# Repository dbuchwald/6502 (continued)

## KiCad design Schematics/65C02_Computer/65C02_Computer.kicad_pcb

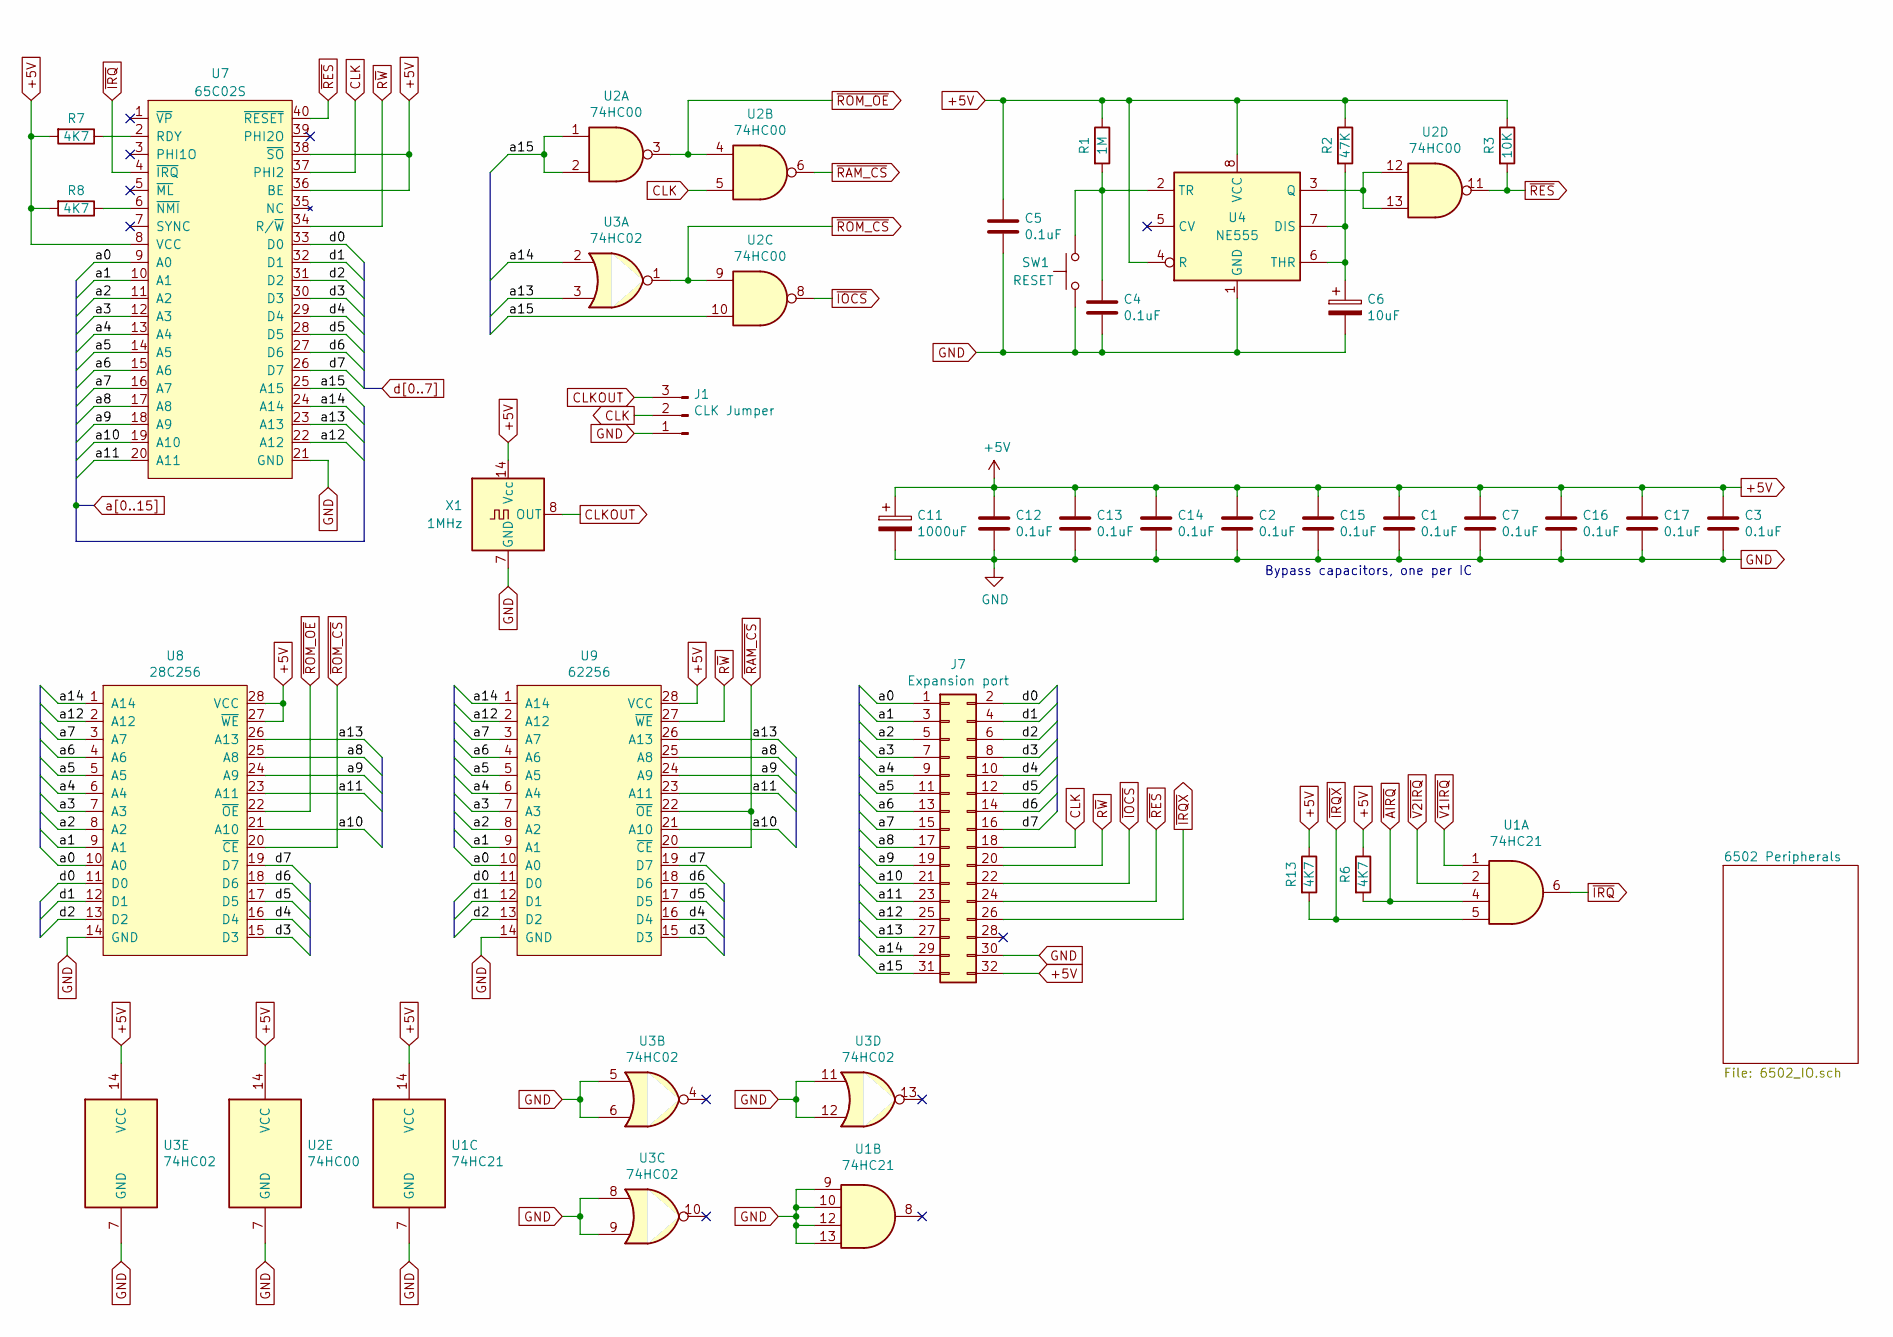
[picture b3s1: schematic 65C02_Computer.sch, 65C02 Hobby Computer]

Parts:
C1, C2, C3, C4, C5, C7, C12, C13, C14, C15, C16, C17: 0.1uF; C_Disc_D3.4mm_W2.1mm_P2.50mm
C6: 10uF; CP_Radial_D5.0mm_P2.50mm
C11: 1000uF; CP_Radial_D10.0mm_P5.00mm
J1: CLK Jumper; PinHeader_1x03_P2.54mm_Vertical
J7: Expansion port; PinSocket_2x16_P2.54mm_Vertical
R1: 1M; R_Axial_DIN0207_L6.3mm_D2.5mm_P7.62mm_Horizontal
R2: 47K; R_Axial_DIN0207_L6.3mm_D2.5mm_P7.62mm_Horizontal
R3: 10K; R_Axial_DIN0207_L6.3mm_D2.5mm_P7.62mm_Horizontal
R6, R7, R8, R13: 4K7; R_Axial_DIN0207_L6.3mm_D2.5mm_P7.62mm_Horizontal
SW1: RESET; SW_PUSH_6mm_H4.3mm
U1: 74HC21; DIP-14_W7.62mm_Socket
U2: 74HC00; DIP-14_W7.62mm_Socket
U3: 74HC02; DIP-14_W7.62mm_Socket
U4: NE555; DIP-8_W7.62mm_Socket
U7: 65C02S; DIP-40_W15.24mm_Socket
U8: 28C256; DIP-28_W15.24mm_Socket
U9: 62256; DIP-28_W15.24mm_Socket
X1: 1MHz; Oscillator_DIP-14

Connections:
+5V: C1.1, C2.1, C3.1, C5.1, C7.1, C11.1, C12.1, C13.1, C14.1, C15.1, C16.1, C17.1, J7.32, R1.1, R2.1, R3.1, R6.1, R7.2, R8.2, R13.1, U1.14 (VCC), U2.14 (VCC), U3.14 (VCC), U4.4 (R), U4.8 (VCC), U7.8 (VCC), U7.36 (BE), U7.38 (~SO), U8.27 (~WE), U8.28 (VCC), U9.28 (VCC), X1.14 (Vcc); also elsewhere on the board
CLK: J1.2, J7.18, U2.5, U7.37 (PHI2); also elsewhere on the board
CLKOUT: J1.3, X1.8 (OUT)
GND: C1.2, C2.2, C3.2, C4.2, C5.2, C6.2, C7.2, C11.2, C12.2, C13.2, C14.2, C15.2, C16.2, C17.2, J1.1, J7.30, SW1.1, U1.7 (GND), U1.9, U1.10, U1.12, U1.13, U2.7 (GND), U3.5, U3.6, U3.7 (GND), U3.8, U3.9, U3.11, U3.12, U4.1 (GND), U7.21 (GND), U8.14 (GND), U9.14 (GND), X1.7 (GND); also elsewhere on the board
unnamed: C4.1, R1.2, SW1.2, U4.2 (TR)
unnamed: C6.1, R2.2, U4.6 (THR), U4.7 (DIS)
unnamed: R7.1, U7.2 (RDY)
unnamed: R8.1, U7.6 (~NMI)
unnamed: U2.12, U2.13, U4.3 (Q)
R~W: J7.20, U7.34 (R/~W), U9.27 (~WE); also elsewhere on the board
a0: J7.1, U7.9 (A0), U8.10 (A0), U9.10 (A0); also elsewhere on the board
a1: J7.3, U7.10 (A1), U8.9 (A1), U9.9 (A1); also elsewhere on the board
a2: J7.5, U7.11 (A2), U8.8 (A2), U9.8 (A2); also elsewhere on the board
a3: J7.7, U7.12 (A3), U8.7 (A3), U9.7 (A3); also elsewhere on the board
a4: J7.9, U7.13 (A4), U8.6 (A4), U9.6 (A4)
a5: J7.11, U7.14 (A5), U8.5 (A5), U9.5 (A5)
a6: J7.13, U7.15 (A6), U8.4 (A6), U9.4 (A6)
a7: J7.15, U7.16 (A7), U8.3 (A7), U9.3 (A7)
a8: J7.17, U7.17 (A8), U8.25 (A8), U9.25 (A8)
a9: J7.19, U7.18 (A9), U8.24 (A9), U9.24 (A9)
a10: J7.21, U7.19 (A10), U8.21 (A10), U9.21 (A10); also elsewhere on the board
a11: J7.23, U7.20 (A11), U8.23 (A11), U9.23 (A11); also elsewhere on the board
a12: J7.25, U7.22 (A12), U8.2 (A12), U9.2 (A12); also elsewhere on the board
a13: J7.27, U3.3, U7.23 (A13), U8.26 (A13), U9.26 (A13)
a14: J7.29, U3.2, U7.24 (A14), U8.1 (A14), U9.1 (A14)
a15: J7.31, U2.1, U2.2, U2.10, U7.25 (A15)
d0: J7.2, U7.33 (D0), U8.11 (D0), U9.11 (D0); also elsewhere on the board
d1: J7.4, U7.32 (D1), U8.12 (D1), U9.12 (D1); also elsewhere on the board
d2: J7.6, U7.31 (D2), U8.13 (D2), U9.13 (D2); also elsewhere on the board
d3: J7.8, U7.30 (D3), U8.15 (D3), U9.15 (D3); also elsewhere on the board
d4: J7.10, U7.29 (D4), U8.16 (D4), U9.16 (D4); also elsewhere on the board
d5: J7.12, U7.28 (D5), U8.17 (D5), U9.17 (D5); also elsewhere on the board
d6: J7.14, U7.27 (D6), U8.18 (D6), U9.18 (D6); also elsewhere on the board
d7: J7.16, U7.26 (D7), U8.19 (D7), U9.19 (D7); also elsewhere on the board
~AIRQ: R6.2, U1.4; also elsewhere on the board
~IOCS: J7.22, U2.8; also elsewhere on the board
~IRQ: U1.6, U7.4 (~IRQ)
~IRQX: J7.26, R13.2, U1.5
~RAM_CS: U2.6, U9.20 (~CE), U9.22 (~OE)
~RES: J7.24, R3.2, U2.11, U7.40 (~RESET); also elsewhere on the board
~ROM_CS: U2.9, U3.1, U8.20 (~CE)
~ROM_OE: U2.3, U2.4, U8.22 (~OE)
~V1IRQ: U1.1; also elsewhere on the board
~V2IRQ: U1.2; also elsewhere on the board

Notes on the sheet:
Bypass capacitors, one per IC

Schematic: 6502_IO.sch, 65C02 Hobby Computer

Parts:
C8: 10nF; C_Disc_D3.4mm_W2.1mm_P2.50mm
C9, C10: 47pF; C_Disc_D3.4mm_W2.1mm_P2.50mm
D1: PWR; LED_D5.0mm_Clear
D2: TX; LED_D5.0mm_Clear
D3: RX; LED_D5.0mm_Clear
D4: BLINK; LED_D5.0mm_Clear
FB1: Ferrite_Bead_Small; R_Axial_DIN0207_L6.3mm_D2.5mm_P7.62mm_Horizontal
J2: Optional UART Port; PinSocket_1x06_P2.54mm_Vertical
J3: USB_B_Micro; USB_Micro-B_Molex-105017-0001
J4: USB_B; USB_B_OST_USB-B1HSxx_Horizontal
J5: Power Connector; BarrelJack_Horizontal
J6: Mini-DIN-6; mini_din-6
J8: AVR-ISP-10; PinHeader_2x03_P2.54mm_Vertical
J9: VIA2PA; PinHeader_1x12_P2.54mm_Vertical
J10: VIA2PB; PinHeader_1x12_P2.54mm_Vertical
J11: LCD Connector; PinSocket_1x16_P2.54mm_Vertical
R4, R5: 27; R_Axial_DIN0207_L6.3mm_D2.5mm_P7.62mm_Horizontal
R9, R10, R11, R12: 270; R_Axial_DIN0207_L6.3mm_D2.5mm_P7.62mm_Horizontal
RV1: 10K; Potentiometer_Piher_PT-10-V10_Vertical
U5: 65C51N; DIP-28_W15.24mm_Socket
U6: FT230XS; SSOP-16_3.9x4.9mm_P0.635mm_long_pads
U10: ATtiny4313-PU; DIP-20_W7.62mm_Socket
U11, U12: 65C22S; DIP-40_W15.24mm_Socket
X2: 1.8432MHz; Oscillator_DIP-14

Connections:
+5V: C8.1, FB1.1, J2.6, J5.1, J6.4, J8.2, J9.12, J10.12, J11.2, J11.15, R12.1, RV1.1, U5.15 (VDD), U6.12 (VCC), U10.20 (VCC), U11.20 (VDD), U12.20 (VDD), X2.14 (Vcc); also elsewhere on the board
/6502 Peripherals/v1pa0: U10.12 (PB0), U12.2 (PA0)
/6502 Peripherals/v1pa1: U10.13 (PB1), U12.3 (PA1)
/6502 Peripherals/v1pa2: U10.14 (PB2), U12.4 (PA2)
/6502 Peripherals/v1pa3: U10.15 (PB3), U12.5 (PA3)
/6502 Peripherals/v1pa4: U10.16 (PB4), U12.6 (PA4)
/6502 Peripherals/v1pa5: J8.4, U10.17 (PB5), U12.7 (PA5)
/6502 Peripherals/v1pa6: J8.1, U10.18 (PB6), U12.8 (PA6)
/6502 Peripherals/v1pa7: J8.3, U10.19 (PB7), U12.9 (PA7)
/6502 Peripherals/v1pa8: U10.3 (PD1), U12.40 (CA1)
/6502 Peripherals/v1pa9: U10.7 (PD3), U12.39 (CA2)
/6502 Peripherals/v1pb0: R9.1, U12.10 (PB0)
/6502 Peripherals/v1pb1: J11.4, U12.11 (PB1)
/6502 Peripherals/v1pb2: J11.5, U12.12 (PB2)
/6502 Peripherals/v1pb3: J11.6, U12.13 (PB3)
/6502 Peripherals/v1pb4: J11.11, U12.14 (PB4)
/6502 Peripherals/v1pb5: J11.12, U12.15 (PB5)
/6502 Peripherals/v1pb6: J11.13, U12.16 (PB6)
/6502 Peripherals/v1pb7: J11.14, U12.17 (PB7)
/6502 Peripherals/v2pa0: J9.1, U11.2 (PA0)
/6502 Peripherals/v2pa1: J9.2, U11.3 (PA1)
/6502 Peripherals/v2pa2: J9.3, U11.4 (PA2)
/6502 Peripherals/v2pa3: J9.4, U11.5 (PA3)
/6502 Peripherals/v2pa4: J9.5, U11.6 (PA4)
/6502 Peripherals/v2pa5: J9.6, U11.7 (PA5)
/6502 Peripherals/v2pa6: J9.7, U11.8 (PA6)
/6502 Peripherals/v2pa7: J9.8, U11.9 (PA7)
/6502 Peripherals/v2pa8: J9.9, U11.40 (CA1)
/6502 Peripherals/v2pa9: J9.10, U11.39 (CA2)
/6502 Peripherals/v2pb0: J10.1, U11.10 (PB0)
/6502 Peripherals/v2pb1: J10.2, U11.11 (PB1)
/6502 Peripherals/v2pb2: J10.3, U11.12 (PB2)
/6502 Peripherals/v2pb3: J10.4, U11.13 (PB3)
/6502 Peripherals/v2pb4: J10.5, U11.14 (PB4)
/6502 Peripherals/v2pb5: J10.6, U11.15 (PB5)
/6502 Peripherals/v2pb6: J10.7, U11.16 (PB6)
/6502 Peripherals/v2pb7: J10.8, U11.17 (PB7)
/6502 Peripherals/v2pb8: J10.9, U11.18 (CB1)
/6502 Peripherals/v2pb9: J10.10, U11.19 (CB2)
CLK: U5.27 (PHI2), U11.25 (PHI2), U12.25 (PHI2); also elsewhere on the board
GND: C8.2, C9.2, C10.2, D1.1 (K), D4.1 (K), J2.5, J3.5 (GND), J4.4 (GND), J5.2, J6.3, J8.6, J9.11, J10.11, J11.1, J11.7, J11.8, J11.9, J11.10, J11.16, RV1.3, U5.1 (VSS), U5.16 (~DCD), U5.17 (~DSR), U6.5 (GND), U6.13 (GND), U10.10 (GND), U11.1 (VSS), U12.1 (VSS), X2.7 (GND); also elsewhere on the board
KBCLK: J6.5, U10.6 (PD2)
KBDAT: J6.1, U10.2 (PD0)
unnamed: D1.2 (A), R12.2
unnamed: D2.1 (K), U6.15 (CBUS0)
unnamed: D2.2 (A), R11.2
unnamed: D3.1 (K), U6.14 (CBUS1)
unnamed: D3.2 (A), R10.2
unnamed: D4.2 (A), R9.2
unnamed: FB1.2, J3.1 (VBUS), J4.1 (VBUS)
unnamed: J11.3, RV1.2
unnamed: R10.1, R11.1, U6.3 (VCCIO), U6.10 (3V3OUT)
PUSBD+: C9.1, J3.3 (D+), J4.3 (D+), R5.2
PUSBD-: C10.1, J3.2 (D-), J4.2 (D-), R4.2
RS232CLK: U5.6 (XTLI), X2.8 (OUT)
RxD: J2.2, U5.12 (RxD), U6.1 (TXD)
R~W: U5.28 (R~W), U11.22 (R~W), U12.22 (R~W); also elsewhere on the board
TxD: J2.1, U5.10 (TxD), U6.4 (RXD)
USBD+: R5.1, U6.8 (USBD+)
USBD-: R4.1, U6.9 (USBD-)
a0: U5.13 (RS0), U11.38 (RS0), U12.38 (RS0); also elsewhere on the board
a1: U5.14 (RS1), U11.37 (RS1), U12.37 (RS1); also elsewhere on the board
a2: U11.36 (RS2), U12.36 (RS2); also elsewhere on the board
a3: U11.35 (RS3), U12.35 (RS3); also elsewhere on the board
a10: U5.2 (CS0); also elsewhere on the board
a11: U11.24 (CS1); also elsewhere on the board
a12: U12.24 (CS1); also elsewhere on the board
d0: U5.18 (D0), U11.33 (D0), U12.33 (D0); also elsewhere on the board
d1: U5.19 (D1), U11.32 (D1), U12.32 (D1); also elsewhere on the board
d2: U5.20 (D2), U11.31 (D2), U12.31 (D2); also elsewhere on the board
d3: U5.21 (D3), U11.30 (D3), U12.30 (D3); also elsewhere on the board
d4: U5.22 (D4), U11.29 (D4), U12.29 (D4); also elsewhere on the board
d5: U5.23 (D5), U11.28 (D5), U12.28 (D5); also elsewhere on the board
d6: U5.24 (D6), U11.27 (D6), U12.27 (D6); also elsewhere on the board
d7: U5.25 (D7), U11.26 (D7), U12.26 (D7); also elsewhere on the board
~AIRQ: U5.26 (~IRQ); also elsewhere on the board
~CTS: J2.4, U5.9 (~CTS), U6.2 (~RTS)
~IOCS: U5.3 (~CS1), U11.23 (~CS2), U12.23 (~CS2); also elsewhere on the board
~RES: J8.5, U5.4 (~RES), U6.11 (~RES), U10.1 (PA2/~RESET), U11.34 (~RES), U12.34 (~RES); also elsewhere on the board
~RTS: J2.3, U5.8 (~RTS), U6.6 (~CTS)
~V1IRQ: U12.21 (~IRQ); also elsewhere on the board
~V2IRQ: U11.21 (~IRQ); also elsewhere on the board

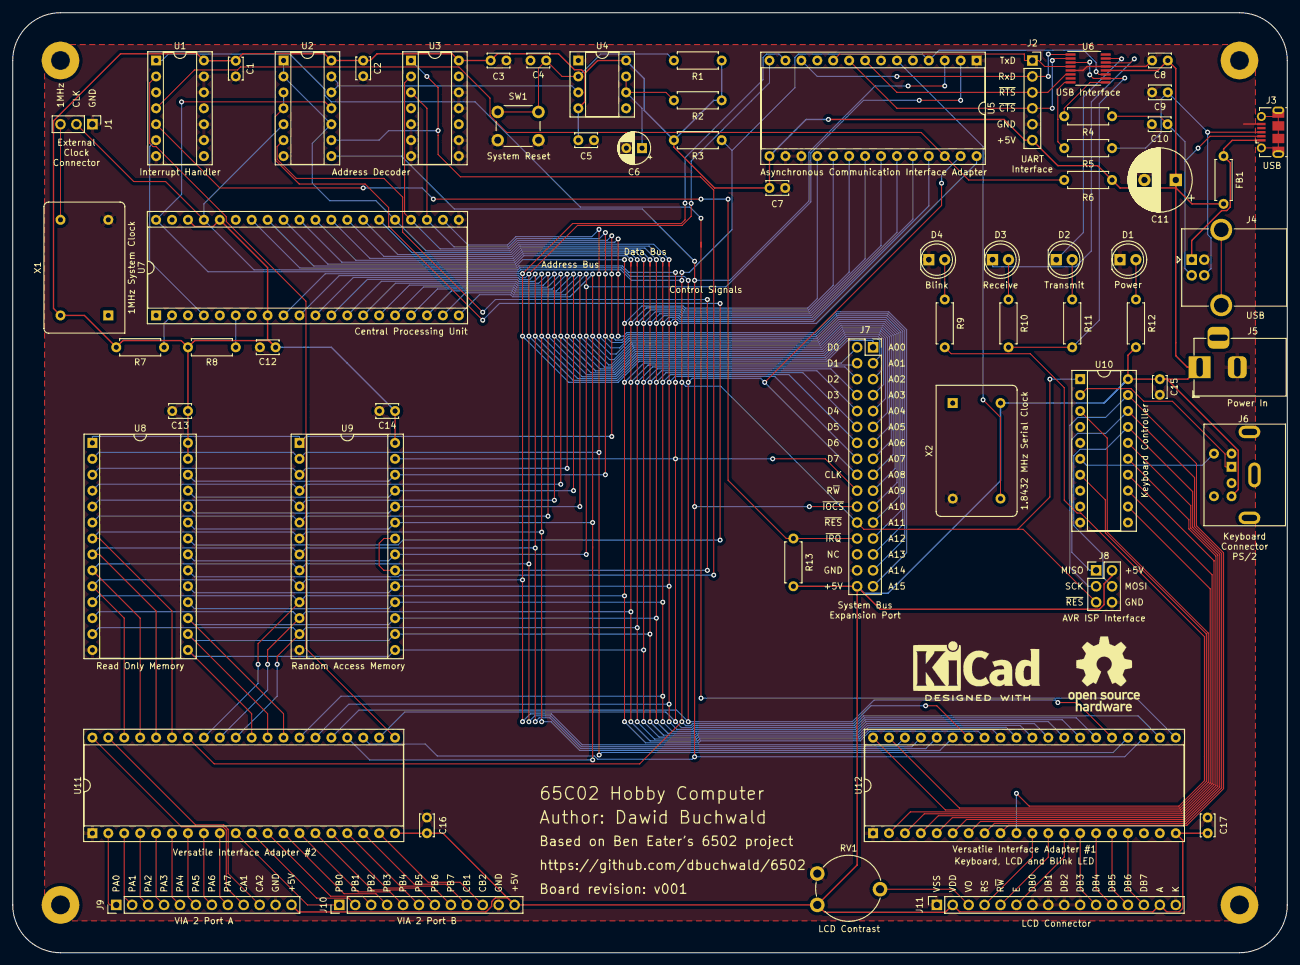
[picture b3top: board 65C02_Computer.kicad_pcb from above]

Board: 2 copper layers, 203.2 x 149.9 mm, 62 parts (0 on the bottom side), 102 nets.

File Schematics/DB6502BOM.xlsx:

Reference | Type | Value | Description | Jameco | DigiKey
C1 | Unpolarized Capacitor | 100 nF | Disk, 2.5mm raster | 151116 | 399-4151-ND
C2 | Unpolarized Capacitor | 100 nF | Disk, 2.5mm raster | 151116 | 399-4151-ND
C3 | Unpolarized Capacitor | 100 nF | Disk, 2.5mm raster | 151116 | 399-4151-ND
C4 | Unpolarized Capacitor | 100 nF | Disk, 2.5mm raster | 151116 | 399-4151-ND
C5 | Unpolarized Capacitor | 100 nF | Disk, 2.5mm raster | 151116 | 399-4151-ND
C6 | Polarized Capacitor | 10 uF | Tube, 2.5mm raster, 5mm diameter | 330692 | 1189-2322-ND
C7 | Unpolarized Capacitor | 100 nF | Disk, 2.5mm raster | 151116 | 399-4151-ND
C8 | Unpolarized Capacitor | 10 nF | Disk, 2.5mm raster |  | 399-4150-ND
C9 | Unpolarized Capacitor | 47 pF | Disk, 2.5mm raster | 2300831 | 399-9737-ND
C10 | Unpolarized Capacitor | 47 pF | Disk, 2.5mm raster | 2300831 | 399-9737-ND
C11 | Polarized Capacitor | 1000 uF | Tube, 5mm raster, 10mm diameter | 330722 | 1189-1745-ND
C12 | Unpolarized Capacitor | 100 nF | Disk, 2.5mm raster | 151116 | 399-4151-ND
C13 | Unpolarized Capacitor | 100 nF | Disk, 2.5mm raster | 151116 | 399-4151-ND
C14 | Unpolarized Capacitor | 100 nF | Disk, 2.5mm raster | 151116 | 399-4151-ND
C15 | Unpolarized Capacitor | 100 nF | Disk, 2.5mm raster | 151116 | 399-4151-ND
C16 | Unpolarized Capacitor | 100 nF | Disk, 2.5mm raster | 151116 | 399-4151-ND
C17 | Unpolarized Capacitor | 100 nF | Disk, 2.5mm raster | 151116 | 399-4151-ND
D1 | LED | Green | 5mm diameter (PWR) | 2279199 | 754-1263-ND
D2 | LED | Red | 5mm diameter (TX) | 333973 | 754-1264-ND
D3 | LED | Green | 5mm diameter (RX) | 2279199 | 754-1263-ND
D4 | LED | Red | 5mm diameter (BLINK) | 333973 | 754-1264-ND
FB1 | Ferrite bead small |  |  | 1844580 | 490-10997-ND
J1 | Pin header 3x1 |  | 2.54mm raster |  | 2057-PH1-03-UA-ND
J2 | Female pin header 6x1 |  | 2.54mm raster |  | S7004-ND
J3 | USB B Micro |  | Molex 105017-0001 |  | WM1399CT-ND
J4 | USB B |  | Standard THT horizontal USB B port | 2096245 | 2057-USB-B-S-RA-ND
J5 | Barrel Jack |  | Standard power input 2.1/5.5 | 101178
J6 | Mini-Din-6 |  | Standard THT PS/2 Keyboard port | 119475 | CP-2260-ND
J7 | Female pin header 16x2 |  | 2.54mm raster |  | S7119-ND
J8 | Pin header 3x2 |  | AVR ISP 2.54mm raster |  | 609-3234-ND
J9 | Pin header 12x1 |  | 2.54mm raster |  | 2057-PH1-12-UA-ND
J10 | Pin header 12x1 |  | 2.54mm raster |  | 2057-PH1-12-UA-ND
J11 | Female pin header 16x1 |  | 2.54mm raster |  | S7049-ND
R1 | Resistor | 1M | 1/4 watt | 691585
R2 | Resistor | 47K | 1/4 watt | 691260
R3 | Resistor | 10K | 1/4 watt | 691104
R4 | Resistor | 27 | 1/4 watt | 690486
R5 | Resistor | 27 | 1/4 watt | 690486
R6 | Resistor | 4K7 | 1/4 watt | 691024
R7 | Resistor | 4K7 | 1/4 watt | 691024
R8 | Resistor | 4K7 | 1/4 watt | 691024
R9 | Resistor | 220 | 1/4 watt | 690700
R10 | Resistor | 220 | 1/4 watt | 690700
R11 | Resistor | 220 | 1/4 watt | 690700
R12 | Resistor | 220 | 1/4 watt | 690700
R13 | Resistor | 4K7 | 1/4 watt | 691260
RV1 | Potentiometer | 10K | Piher PT10-LV10-103 |  | 1993-1116-ND
SW1 | Pushbutton |  | Standard 6mm THT pushbutton | 149948
U1 | IC | 74HC21 |  | 2285255 | 296-8266-5-ND
U1 | Socket | 14-pin |  | 37197 | ED3314-ND
U2 | IC | 74HC00 |  | 45161 | 296-1563-5-ND
U2 | Socket | 14-pin |  | 37197 | ED3314-ND
U3 | IC | 74HC02 |  | 45188 | 296-1564-5-ND
U3 | Socket | 14-pin |  | 37197 | ED3314-ND
U4 | IC | NE555 |  | 27422 | 296-NE555P-ND
U4 | Socket | 8-pin |  | 51626 | ED90048-ND
U5 | IC | 6551 | ACIA chip, see notes below | 43318
U6 | IC | FT230XS |  |  | 768-1135-1-ND
U7 | IC | 65C02S |  | 2143638
U7 | Socket | 40-pin |  | 41136 | ED90059-ND
U8 | IC | 28C256 |  | 74843 | AT28C256-15PU-ND
U8 | Socket | 28-pin | Order two | 2289583 | ED90520-ND
U9 | IC | 62256 |  | 82472 | 1450-1480-ND
U9 | Socket | 28-pin |  | 2289583 | ED90520-ND
U10 | IC | ATtiny4313-PU | Add socket |  | ATTINY4313-PU-ND
U10 | Socket | 20-pin |  | 38623 | ED90036-ND
U11 | IC | 65C22S |  | 2143591
U11 | Socket | 40-pin |  | 41136 | ED90059-ND
U12 | IC | 65C22S |  | 2143591
U12 | Socket | 40-pin |  | 41136 | ED90059-ND
X1 | Crystal Oscillator | 1MHz |  | 27861 | X937-ND
X2 | Crystal Oscillator | 1.8432MHz |  | 27879 | X939-ND

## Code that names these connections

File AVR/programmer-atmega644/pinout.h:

#ifndef __PINOUT_H__DEFINED
#define __PINOUT_H__DEFINED

#define ADDRMSB_DDR  DDRC
#define ADDRLSB_DDR  DDRA
#define DATA_DDR     DDRB
#define CONTROL_DDR  DDRD

#define ADDRMSB_POUT PORTC
#define ADDRLSB_POUT PORTA
#define DATA_POUT    PORTB
#define CONTROL_POUT PORTD

#define ADDRMSB_PIN  PINC
#define ADDRLSB_PIN  PINA
#define DATA_PIN     PINB
#define CONTROL_PIN  PIND

#define SR_DAT       _BV(PD2)
#define SR_CLK       _BV(PD3)
#define SR_OUT       _BV(PD4)

#define CLK_BIT      _BV(PD5)
#define RW_BIT       _BV(PD6)
#define SYNC_BIT     _BV(PD7)

#define CLKSEL_BIT   _BV(0)
#define BE_BIT       _BV(1)
#define RDY_BIT      _BV(2)
#define RESET_BIT    _BV(7)

#define ALL_INPUT    0x00
#define ALL_OUTPUT   0xff
#define ALL_PULL_UP  0xff

#endif

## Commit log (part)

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2020-04-01 Changed ZP variable name
2020-04-01 Added missing message
2020-04-01 Added system break test
2020-04-02 Major rebranding and credits
2020-04-02 Create LICENSE
2020-04-02 Added tokenize tests to string testing module
2020-04-03 First implementation of generic menu feature
2020-04-04 Implemented basic parse functions
2020-04-04 Moved parser and menu routines to common library
2020-04-05 Corrected macro
2020-04-05 Refactoring in progress
2020-04-05 Fixed system break bug
2020-04-05 Fixed broken macro
2020-04-05 Fixed parse issue
2020-04-05 Reimplemented monitor and simple shell using menu
2020-04-06 Address mode refactoring
2020-04-06 Initial monitor implementation
2020-04-07 Implemented missing LCD TTY routines, fixed some bugs
2020-04-07 Common library analyzed for C compatibility
2020-04-07 Added opcodes matrix for disassembler
2020-04-08 Corrected issue #34
    Corrected pot value for clock frequency regulator
2020-04-08 Moved strcpy to common string routines
2020-04-08 Added disassembly function to monitor app
2020-04-09 Resolved #36, partially implemented #28
2020-04-10 Initial implementation - not working
2020-04-10 Updated parse routines
2020-04-10 Refactored blink operation, added C bindings
2020-04-10 Provided ACIA bindings for C
2020-04-11 Fixed issue with last commit
2020-04-14 Implemented C bindings for LCD
2020-04-14 Added C bindings for some C functions
2020-04-14 C bindins for TTY operations
2020-04-14 Fixed issue with disassembler operation
2020-04-15 Added remaining string functions C bindings
2020-04-15 Created C bindings for remaining LCD routines
2020-04-15 C bindings for parse functions
2020-04-15 Fixed issue with C stack leakage
2020-04-15 Resolved #23
2020-04-16 Another small fix
2020-04-16 Fixed merge issue
2020-04-17 Created C binding for menu functionality
2020-04-17 Small updates
2020-04-17 Improved menu handling
2020-04-18 Implemented C binding for conver_to_hex function
2020-04-18 Completed build process change to include C library
2020-04-18 Updated OS version number
2020-04-18 Remove n/a
2020-04-18 DigiKey links
2020-04-21 Correct part number for 28-pin socket
2020-04-21 Redesigned zeropage memory handling
2020-04-21 Fixed more MicroChess issues
2020-04-21 Moved common function to syscall vector
2020-04-25 Refactored LCD code to mention 4-bit explicitly
2020-04-28 Added new parse function for decimal numbers
2020-04-29 Initial implementation of basic parser
2020-04-30 Added hello world examples for presentation
2020-04-30 Resolved issue #40
2020-04-30 Added string parsing and error handling
2020-04-30 Moved quit command to parser
2020-05-03 Moved token definitions to separate module
2020-05-03 Optimized memory usage
2020-05-05 Run now works correctly
2020-05-05 Added user break functionality
2020-05-06 Added MEM operation to BASIC
2020-05-06 Resolved issue #47
2020-05-06 Improved variable section handling
2020-05-06 Added failed line listing
2020-05-11 Support for WDC65C51 and 8MHz clock
2020-06-23 Partial improvement (not fixed)
2020-06-23 Tweaked BF check loop
2020-06-23 Applied fix to 8bit mode as well
2020-06-24 Added system information command
2020-07-01 Changed some parameters for R6551
2020-07-01 Integrated into build process
2020-07-01 First working version of Microsoft BASIC
2020-07-01 Added DB6502 hello message
2020-07-02 Initial version of non-zp branch
2020-07-02 Fixed line numbering issue on non-ZP inputbuffer
2020-07-02 Renamed file to avoid potential conflict
2020-07-02 First integration with some OS/1 routines
2020-07-02 Minor tweaks
2020-07-02 Corrected compilation issue
2020-07-02 Working loadable module with some improvements
2020-07-02 Added file to track necessary changes
2020-07-02 Implemented EXIT keyword to exit the interpreter
2020-07-02 Added loadable BASIC to main makefile
2020-07-03 Removed self-modifying code and reduced ZP footprint
2020-07-03 Added ZP cleanup on restart, went back to 8MHz
2020-07-06 Preparing config for USBAsp
2020-07-06 Updated makefile for MacOS
2020-07-07 Hello world example for UART
2020-07-08 Implemented first draft of debug program
2020-07-08 Fixed port inputs (they do work now)
2020-07-10 Added simple T! timer program
2020-07-10 Added support for arbitrary clock modes
2020-07-10 Added stub for UI function
2020-07-12 Using direct UART communication
2020-07-13 Almost fully functional BE6502 debugger
2020-07-14 Moved "STACK" to 0x0e00
2020-07-14 Separated STACK from "STACK" :)
2020-07-18 Documentation update
2020-07-18 Removed last reference to FASTCLOCK
2020-07-18 Added XLSX files with 6502 BOM
2020-07-20 First version of DUART schematic
    Initial revision (draft)
2020-07-21 Initial working version (still unstable!)
2020-07-22 Implemented working version of user IRQ example
2020-07-22 Modules referencing VIA no longer need to be static
2020-07-22 Completed VIA2 API and fixed user IRQ issues
2020-07-22 Added CRLF to message
2020-07-22 Fix for uChess provided by /u/tonylweil
2020-07-22 Fixed nasty uChess bug with zeropage access violation
2020-07-23 Working version of async interface with DUART
2020-07-23 Replaced can with crystal, removed unused connections
2020-07-23 First of many commits to refactor serial
2020-07-23 Remaining references to ACIA removed
2020-07-23 Minor fixes to otherwise working code :)
2020-07-23 Small fix of a big bug
2020-07-26 Updated programs list
2020-07-28 Added support for multiple channels
2020-07-28 Moved hardware specific code to separate module
2020-07-28 Separated code between R6551 and WDC65C51
2020-07-30 Performance update for wdc65c51 driver
2020-07-30 First draft version of driver for SC26C92
2020-08-06 Updated MS BASIC to latest source available
2020-08-06 Minor fix for unused code
2020-08-14 Implemented base functions for AT28C256 operation
2020-08-14 Updates to schematic
2020-08-17 Added single gate ICs for clock selection and automatic SR reset
2020-08-18 Changed 74LVC1G126 to 74LVC1G125 for low-active OE
2020-08-24 Fixed issue with UART initialization
2020-08-24 Basic EEPROM dump works now
2020-08-24 Working version of SDP handling and single byte write
2020-08-25 Added SDP routines
2020-08-25 SDP code refactoring
2020-08-27 Working implementation of EEPROM programmer
2020-08-27 Added printable chars output to dump operation
2020-08-30 Solved issues with lrzsz on MacOS
2020-09-01 Small code cleanup
2020-09-01 Got rid of magic numbers in the code
2020-09-04 Finally figured out timers in AVR...
2020-09-10 Refactoring PLD code
2020-09-10 Further PLA code refactoring with better tests
2020-09-14 Implemented POV Toy (side project)
2020-09-16 Initial revision of prototyping board
2020-09-17 PCB layout RC1
2020-09-17 Ordered DB6502 proto PCB
2020-09-18 Small correction to bus markings
2020-09-19 Generated new set of gerber files with the USB correction
2020-09-23 Fixed issue with AVR ISP port horizontal flip
2020-09-23 AVR ISP connections cleanup
2020-09-23 First implementation of single stepping mode
2020-09-23 Created config file for version 2 prototype
2020-09-28 Added two variants of run operation to monitor
2020-09-29 Added support for opcode decoding
2020-10-04 Moved opcode constants to PROGMEM
2020-10-04 Added missing ROM to common makefile
2020-10-05 Added serial test programs for WDC ACIA
2020-10-06 Added reset operation to EEPROM write
2020-10-06 Renamed ACIA to generic SERIAL
2020-10-07 Minor improvements to build process
2020-10-10 Added single instruction stepping to supervisor
2020-10-10 Fixed issues with instructions stack
2020-10-10 Going fast populates cycle buffer now
2020-10-12 Cycle buffer init or reset, code clarity improved
2020-10-13 Fixed issue with clean target
2020-10-13 Started documenting current system layout
2020-10-19 Updated supervisor schematic
2020-10-19 Improvement to build process, added clock control
2020-10-19 Removed remaining .gitignore file
2020-10-20 Implemented wait state generator, cleaned up schematic
2020-10-20 Replaced hardcoded values with defines
2020-10-20 Improved layout of the I/O schematic
2020-10-20 Fixed issue with UART CEN during low clock, added IRQ gate
2020-10-21 Implemented fix for metastability issue during clock switch
2020-10-23 Implemented selection of variable clock driver
2020-10-23 Added dynamic CPU frequency calculation
2020-10-24 Serious improvements to build process
2020-10-25 Added second USB channel to UART
2020-10-26 Corrected clock speed calculation
2020-10-26 Changed loadable MS BASIC to use fixed memory limit
2020-11-01 Added wait state generator logic in PLD
2020-11-02 Updated schematic to reflect PLD WS generator
2020-11-03 Massive cleanup of the schematic
2020-11-03 Cleanup of the datasheets
2020-11-03 Added support for minus 1.5 RDY
2020-11-03 Moved existing decoder code to separate folder
2020-11-03 Implemented example output flip-flop
2020-11-03 Second attempt at simple flip-flop test
2020-11-03 Replaced nWE with nWR and nOE with nRD
2020-11-03 Updated schematic to reflect new wait state generator design
2020-11-05 Implemented WS_DISABLE function
2020-11-12 Upgraded speed to 115200 baud
2020-12-09 First articles converted to Markdown
2020-12-09 Fixed issue with incorrect image path
2020-12-10 Added rest of the articles
2020-12-14 Started writing new project log
2020-12-16 Blog entry about wait states
2020-12-23 Work in progress
2020-12-27 Corrected small typos
2021-01-04 Started working on next article
2021-01-16 Added memory access timing section
2021-01-19 Added ws generator schematics
2021-01-20 More updates
2021-01-30 FInalised 14MHz timing entry
2021-02-26 Added first diagram for RDY signal
2021-02-26 Drafted four schematics for RDY experiments
2021-02-27 Updated the last entry
2021-02-28 Added section about the ringing
2021-02-28 Small correction
2021-03-07 Working on a PCB - first traces routed
2021-03-08 Most chips placed, tracing continues
2021-03-09 Moved things around, board starts to have shape
2021-03-09 Increased capacitor footprints to 1206
2021-03-11 Updates and fixes
2021-03-13 Cache updates
2021-03-13 Some small additions (missing routes)
2021-03-29 Some schematic updates for new port layout
2021-04-03 Fixed small typos
2021-04-09 Added article about adjustable load
2021-04-29 Working on a PCB
2021-05-01 Small fixes on PCB
2021-05-04 PCB Initial draft (no errors in DRC)
2021-05-04 Moving things around
2021-05-04 Further improvements
2021-05-04 Added bus labels
2021-05-05 Added one last line to the system
2021-05-06 PCB RC1
2021-05-10 Last minute updates (remove VCC from AVRISP)
2021-05-17 Started entry on PCB cost
2021-05-21 Simplified RD/WR
2021-05-21 Changed device id
2021-05-31 Working on PCB summary notes
2021-06-02 Updated PCB summary entry
2021-06-03 Working on important update
2021-06-03 Finished entry on PCB summary
2021-06-08 Solved problem with copy-paste distortions
2021-06-10 Typing typing typing
2021-06-11 Completed entry on copy/paste distortion
2021-06-13 Added PLD config for 10ns/14MHz operation
2021-06-13 Compiled with simulation errors
2021-06-14 Started entry on ROM issues
2021-06-14 More updates on the ROM flashing issue
2021-06-15 Finalised entry
2021-06-18 Small improvements to supervisor software
2021-06-20 Finalised entry on 16MHz
2021-06-24 Added system routines for Latch operation
2021-06-24 Enabled parsing of odd length hex numbers
2021-06-25 Added support for EXRAM in supervisor software
2021-07-15 Working on massively redesigned board
2021-08-11 Set up simple library structure for TMS9918 Support
2021-08-11 Fix screen clear util
2021-08-12 vdp - set up macros, zp area, and bug fixes
2021-08-14 rework zp addresses + cleanup
2021-08-14 Basic VRAM copy
2021-08-14 Supports backspace, enter, and escape
2021-08-15 Bug fixes and cursor control
2021-08-15 refine VDP zero page values (wip)
2021-08-16 clean up and fix issues with scrolling code
2021-08-16 relocate text mode utility functions.
2021-08-16 Clean up - simple editor is 'done'
2021-08-16 Initial MSBasic Support
2021-08-17 Add a Clear Screen command to demo adding new commands
2021-08-17 Confirm Shell works with VDP
2021-09-04 Second sound Demo + Initial MidiDemo (WIP)
2021-09-05 Set up Midi shared library
2021-09-06 Functional - basic song loaded.
2021-09-12 Clean up MidiDemo
2021-11-11 Created control plane schema
